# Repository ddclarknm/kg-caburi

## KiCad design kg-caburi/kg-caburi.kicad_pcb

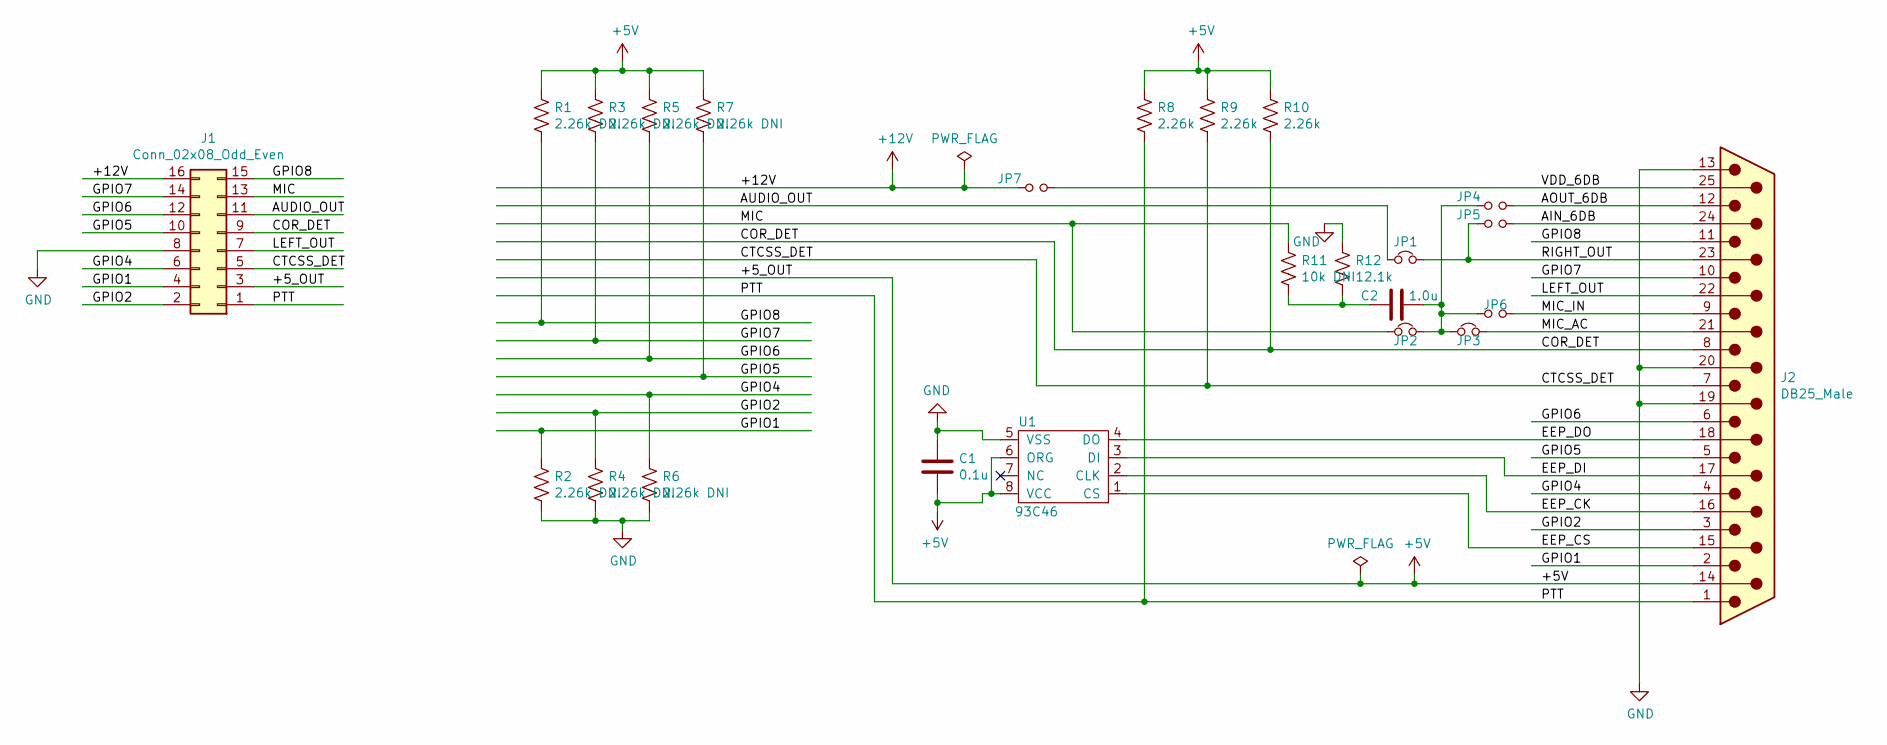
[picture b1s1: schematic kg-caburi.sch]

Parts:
C1: 0.1u; C_0402_1005Metric; Manufacturer Part Number CL05B104KO5NNNC; LCSC C1525
C2: 1.0u; C_0805_2012Metric_Pad1.15x1.40mm_HandSolder; Manufacturer Part Number CL21B105KBFNNNE; LCSC C28323
J1: Conn_02x08_Odd_Even; PinHeader_2x08_P2.00mm_Vertical
J2: DB25_Male; DSUB-25_Male_EdgeMount_P2.77mm
JP1, JP2, JP3: Jumper_NC_Small; SolderJumper-2_P1.3mm_Bridged_RoundedPad1.0x1.5mm
JP4, JP5, JP6, JP7: Jumper_NO_Small; SolderJumper-2_P1.3mm_Open_RoundedPad1.0x1.5mm
R1, R2, R3, R4, R5, R6, R7: 2.26k DNI; R_0805_2012Metric_Pad1.15x1.40mm_HandSolder; Manufacturer Part Number RMCF0805FT2K26
R8, R9, R10: 2.26k; R_0805_2012Metric_Pad1.15x1.40mm_HandSolder; Manufacturer Part Number 0805W8F2261T5E; LCSC C17519
R11: 10k DNI; R_0805_2012Metric_Pad1.15x1.40mm_HandSolder; Manufacturer Part Number 0805W8F1002T5E
R12: 12.1k; R_0805_2012Metric_Pad1.15x1.40mm_HandSolder; Manufacturer Part Number 0805W8F1212T5E; LCSC C17431
U1: 93C46; TSSOP-8_4.4x3mm_P0.65mm; Manufacturer Part Number FT93C46A-UTG-T; LCSC C232890

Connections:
+5V: C1.2, J1.3, J2.14, R1.1, R3.1, R5.1, R7.1, R8.1, R9.1, R10.1, U1.6 (ORG), U1.8 (VCC)
+12V: J1.16, JP7.1
/AIN_6DB: J2.24, JP5.2
/AOUT_6DB: J2.12, JP4.2
/AUDIO_OUT: J1.11, JP1.1
/COR_DET: J1.9, J2.8, R10.2
/CTCSS_DET: J1.5, J2.7, R9.2
/EEP_CK: J2.16, U1.2 (CLK)
/EEP_CS: J2.15, U1.1 (CS)
/EEP_DI: J2.17, U1.3 (DI)
/EEP_DO: J2.18, U1.4 (DO)
/GPIO1: J1.4, J2.2, R2.1
/GPIO2: J1.2, J2.3, R4.1
/GPIO4: J1.6, J2.4, R6.1
/GPIO5: J1.10, J2.5, R7.2
/GPIO6: J1.12, J2.6, R5.2
/GPIO7: J1.14, J2.10, R3.2
/GPIO8: J1.15, J2.11, R1.2
/LEFT_OUT: J1.7, J2.22
/MIC: J1.13, JP2.1, R11.2
/MIC_AC: J2.21, JP3.2
/MIC_IN: J2.9, JP6.2
/PTT: J1.1, J2.1, R8.2
/RIGHT_OUT: J2.23, JP1.2, JP5.1
/VDD_6DB: J2.25, JP7.2
GND: C1.1, J1.8, J2.13, J2.19, J2.20, R2.2, R4.2, R6.2, R12.1, U1.5 (VSS)
unnamed: C2.1, JP2.2, JP3.1, JP4.1, JP6.1
unnamed: C2.2, R11.1, R12.2

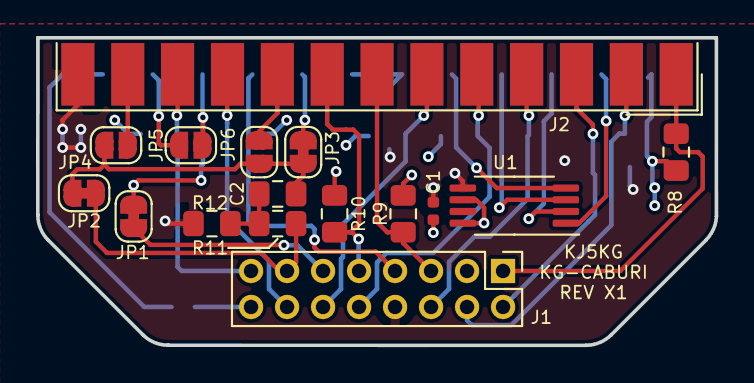
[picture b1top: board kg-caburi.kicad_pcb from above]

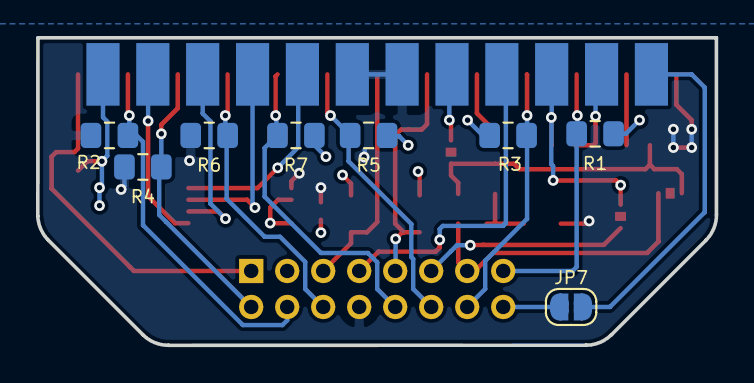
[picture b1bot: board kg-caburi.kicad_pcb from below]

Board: 4 copper layers, 37.7 x 17.1 mm, 24 parts (8 on the bottom side), 28 nets.

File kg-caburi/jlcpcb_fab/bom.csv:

Comment,Designator,Footprint,LCSC
93C46,U1,Package_SO:TSSOP-8_4.4x3mm_P0.65mm,C232890
Jumper_NC_Small,"JP1,JP2,JP3",Jumper:SolderJumper-2_P1.3mm_Bridged_RoundedPad1.0x1.5mm,
Jumper_NO_Small,"JP5,JP4,JP6,JP7",Jumper:SolderJumper-2_P1.3mm_Open_RoundedPad1.0x1.5mm,
DB25_Male,J2,Connector_Dsub:DSUB-25_Male_EdgeMount_P2.77mm,
0.1u,C1,Capacitor_SMD:C_0402_1005Metric,C1525
2.26k,"R8,R9,R10",Resistor_SMD:R_0805_2012Metric_Pad1.15x1.40mm_HandSolder,C17519
Conn_02x08_Odd_Even,J1,Connector_PinHeader_2.00mm:PinHeader_2x08_P2.00mm_Vertical,
12.1k,R12,Resistor_SMD:R_0805_2012Metric_Pad1.15x1.40mm_HandSolder,C17431
10k DNI,R11,Resistor_SMD:R_0805_2012Metric_Pad1.15x1.40mm_HandSolder,
1.0u,C2,Capacitor_SMD:C_0805_2012Metric_Pad1.15x1.40mm_HandSolder,C28323
2.26k DNI,"R1,R3,R5,R7,R2,R4,R6",Resistor_SMD:R_0805_2012Metric_Pad1.15x1.40mm_HandSolder,

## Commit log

2021-03-03 X1 Version sent to JLCPCB for fab
